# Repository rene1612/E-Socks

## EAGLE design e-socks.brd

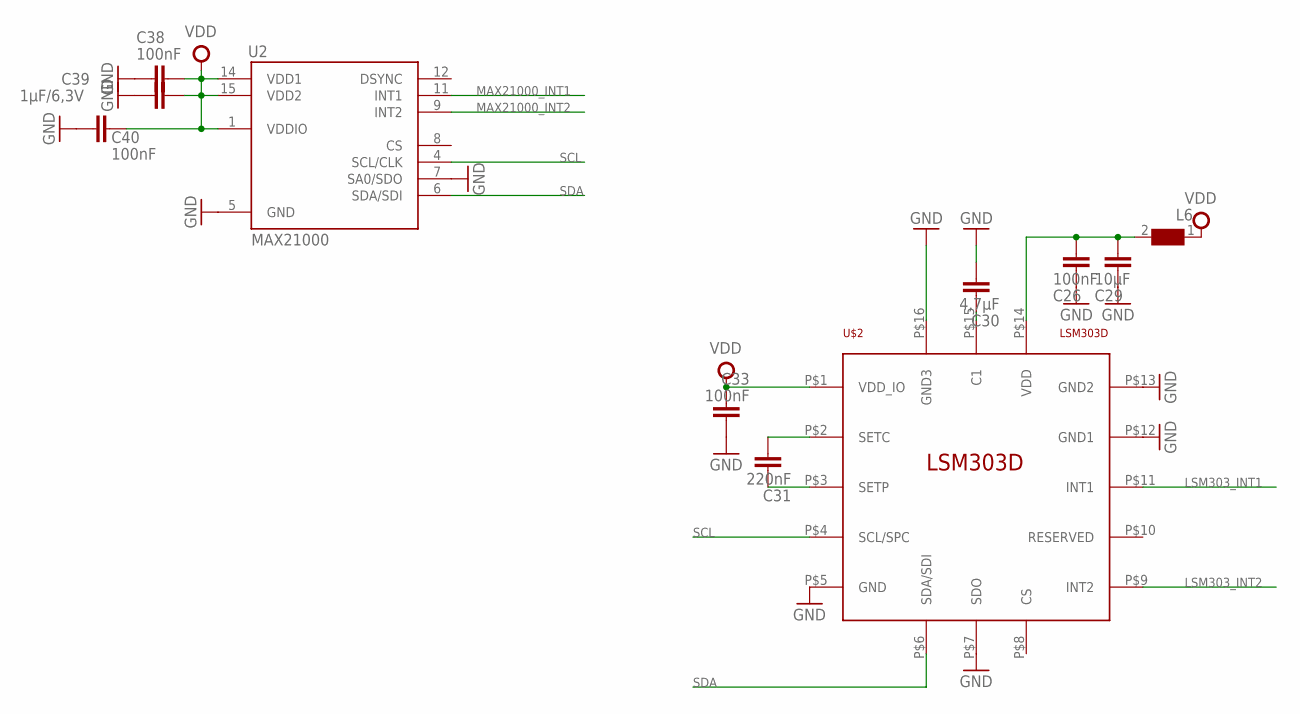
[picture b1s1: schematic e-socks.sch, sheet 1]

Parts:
C26, C33, C38, C40: 100nF; C0402
C29: 10µF; C0402
C30: 4,7µF; C0402
C31: 220nF; C0402
C39: 1µF/6,3V; C0402
L6: WE-CBF_0402; 0402
U2: MAX21000; 16LGA
U$2: LSM303D; TFLGA16L

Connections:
GND: C26.2, C29.2, C30.1, C33.1, C38.2, C39.2, C40.2, U2.5 (GND), U2.7 (SA0/SDO), U$2.P$5 (GND), U$2.P$7 (SDO), U$2.P$12 (GND1), U$2.P$13 (GND2), U$2.P$16 (GND3); also elsewhere on the board
LSM303_INT1: U$2.P$11 (INT1); also elsewhere on the board
LSM303_INT2: U$2.P$9 (INT2)
MAX21000_INT1: U2.11 (INT1); also elsewhere on the board
MAX21000_INT2: U2.9 (INT2)
unnamed: C26.1, C29.1, L6.2, U$2.P$14 (VDD)
unnamed: C31.1, U$2.P$2 (SETC)
unnamed: C31.2, U$2.P$3 (SETP)
unnamed: C30.2, U$2.P$15 (C1)
SCL: U2.4 (SCL/CLK), U$2.P$4 (SCL/SPC); also elsewhere on the board
SDA: U2.6 (SDA/SDI), U$2.P$6 (SDA/SDI); also elsewhere on the board
VDD: C33.2, C38.1, C39.1, C40.1, L6.1, U2.1 (VDDIO), U2.14 (VDD1), U2.15 (VDD2), U$2.P$1 (VDD_IO); also elsewhere on the board

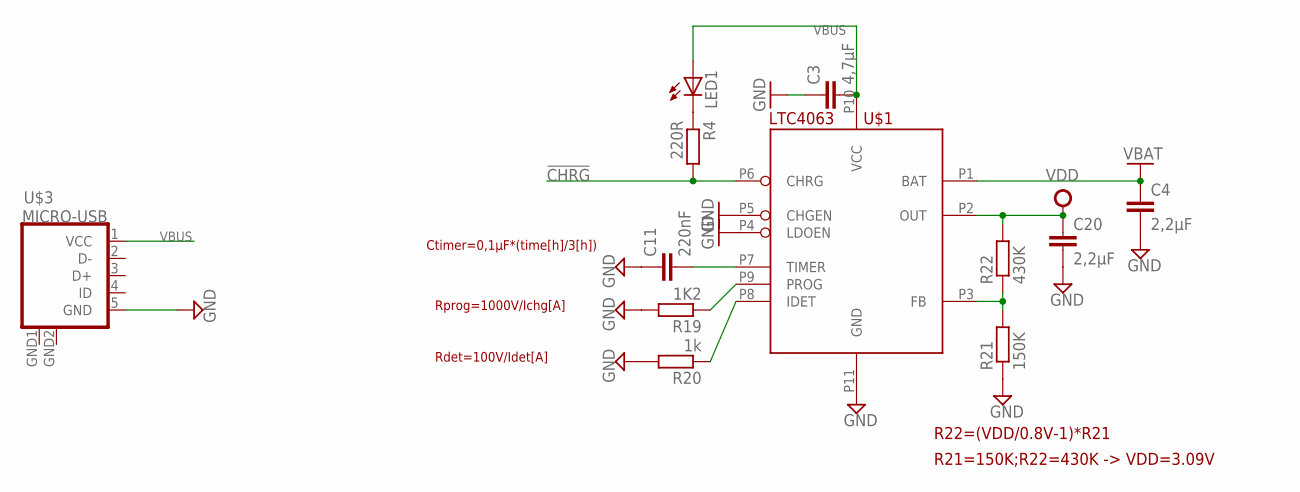
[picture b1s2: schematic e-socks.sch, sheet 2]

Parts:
C3: 4,7µF; C0402
C4, C20: 2,2µF; C0402
C11: 220nF; C0402
LED1: LEDCHIP-LED0603; CHIP-LED0603
R4: 220R; R0402
R19: 1K2; R0402
R20: 1k; R0402
R21: 150K; R0402
R22: 430K; R0402
U$1: LTC4063
U$3: MICRO-USB

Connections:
!CHRG: R4.2, U$1.P6 (CHRG); also elsewhere on the board
GND: C3.1, C4.2, C11.1, C20.2, R19.2, R20.2, R21.1, U$1.P4 (LDOEN), U$1.P5 (CHGEN), U$1.P11 (GND), U$3.5 (GND), U$3.GND1 (GND), U$3.GND2 (GND); also elsewhere on the board
unnamed: C11.2, U$1.P7 (TIMER)
unnamed: R20.1, U$1.P8 (IDET)
unnamed: R21.2, R22.1, U$1.P3 (FB)
unnamed: R19.1, U$1.P9 (PROG)
unnamed: LED1.C, R4.1
VBAT: C4.1, U$1.P1 (BAT); also elsewhere on the board
VBUS: C3.2, LED1.A, U$1.P10 (VCC), U$3.1 (VCC)
VDD: C20.1, R22.2, U$1.P2 (OUT); also elsewhere on the board

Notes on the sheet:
Ctimer=0,1µF*(time[h]/3[h])
Rprog=1000V/Ichg[A]
Rdet=100V/Idet[A]
R22=(VDD/0.8V-1)*R21
R21=150K;R22=430K -> VDD=3.09V

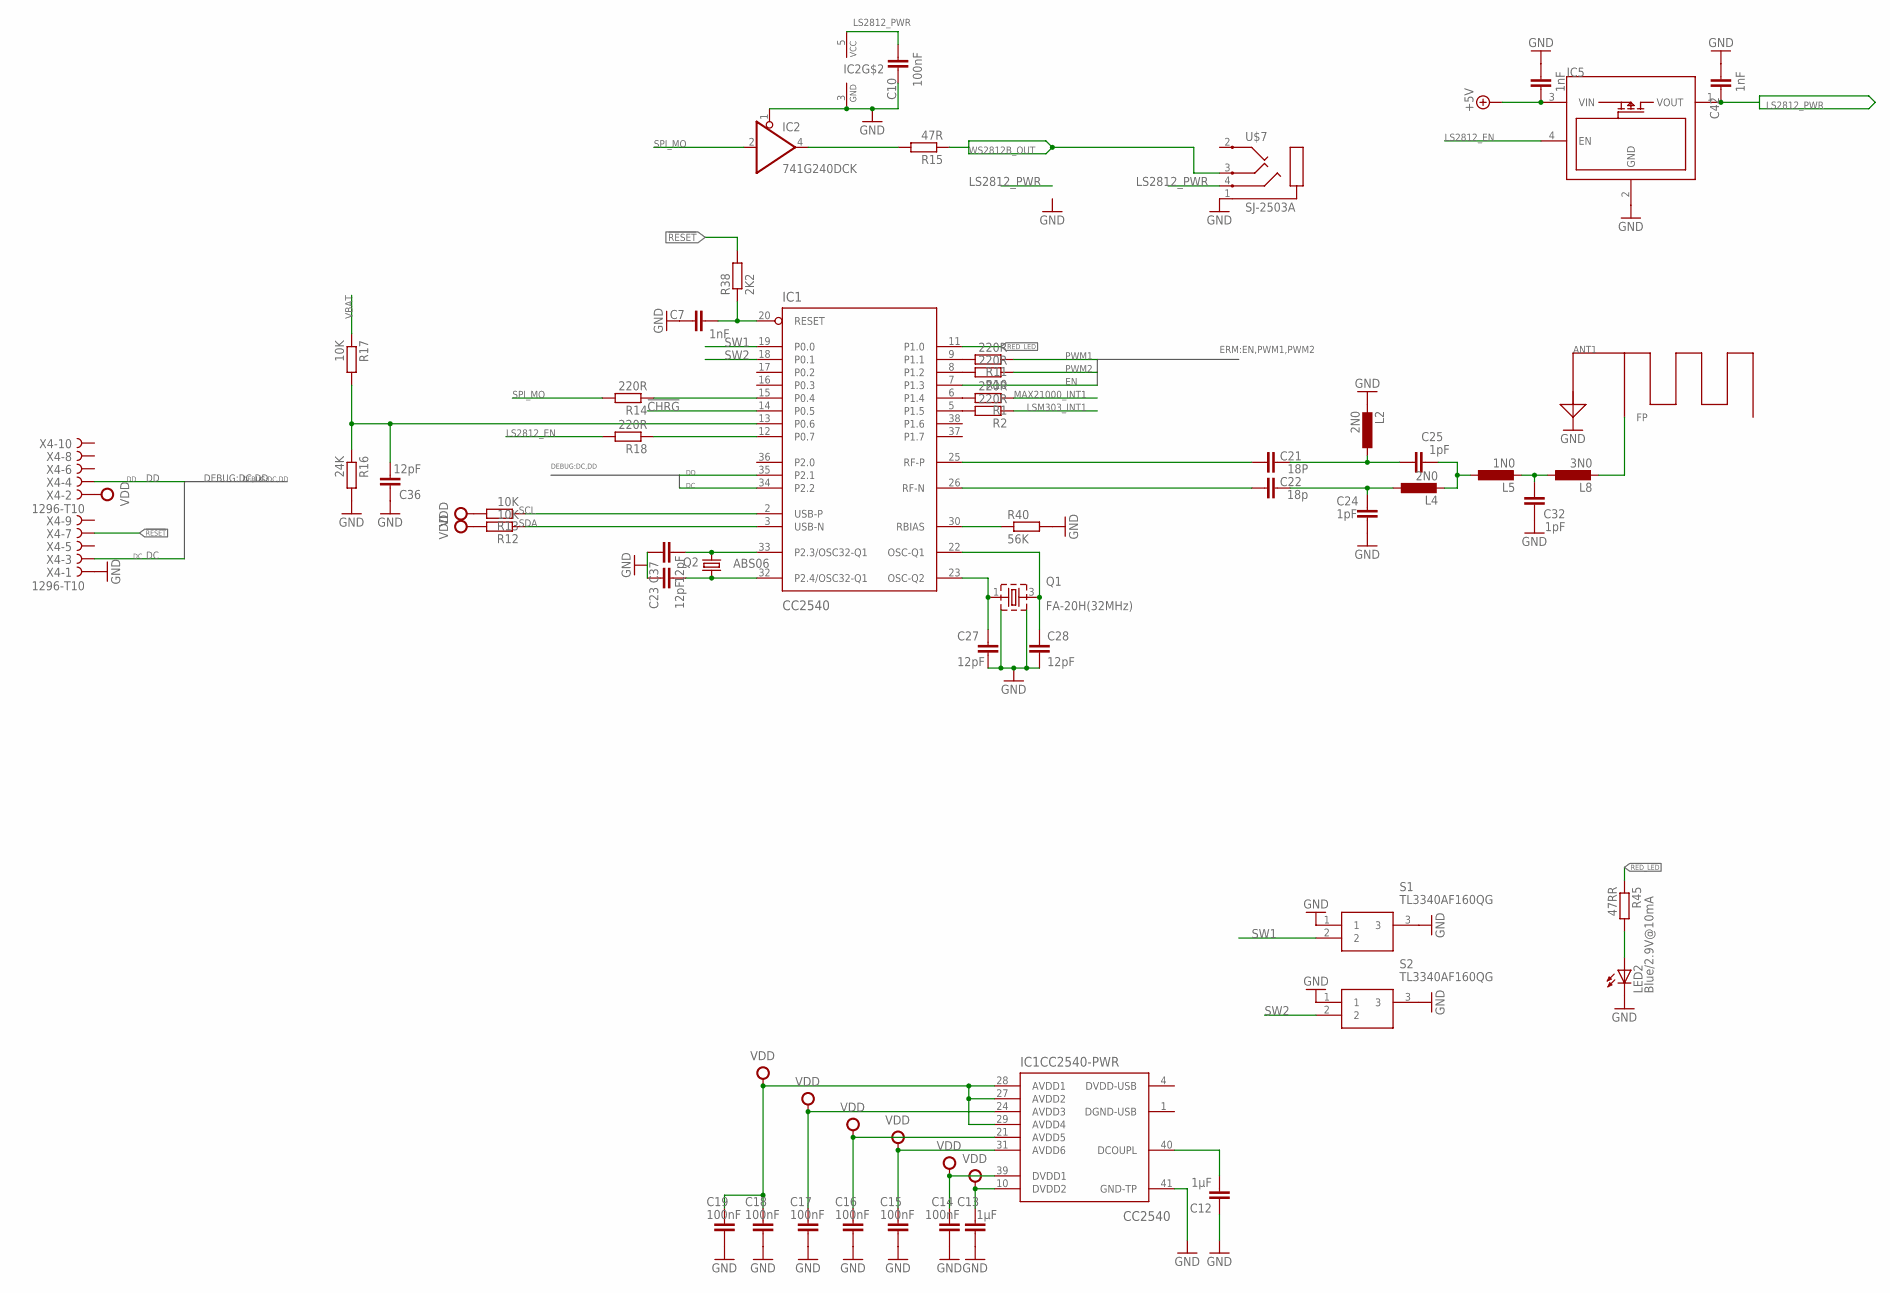
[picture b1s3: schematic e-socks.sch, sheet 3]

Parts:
ANT1: MIFA
C7, C41, C42: 1nF; C0402
C10, C14, C15, C16, C17, C18, C19: 100nF; C0402
C12, C13: 1µF; C0402
C21: 18P; C0402
C22: 18p; C0402
C23, C27, C28, C36, C37: 12pF; C0402
C24, C25, C32: 1pF; C0402
IC1: CC2540; QFN50P600X600X100-41N
IC2: 741G240DCK; SC70-5
IC5: MIC94040
L2, L4: 2N0; L0402
L5: 1N0; L0402
L8: 3N0; L0402
LED2: Blue/2.9V@10mA; CHIP-LED0603
Q1: FA-20H(32MHz); FA-20H
Q2: ABS06
R1, R2, R10, R11, R14, R18: 220R; R0402
R12, R13, R17: 10K; R0402
R15: 47R; R0402
R16: 24K; R0402
R38: 2K2; R0402
R40: 56K; R0402
R45: 47RR; R0402
S1, S2: TL3340AF160QG; TL3340
U$7: SJ-2503A; SJ-2503
X4: 1296-T10; 1296-10

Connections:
!CHRG: IC1.14 (P0.5); also elsewhere on the board
!RESET: R38.2, X4.7
!RESET_INTERN: C7.2, IC1.20 (RESET), R38.1
+5V: C41.1, IC5.3 (VIN); also elsewhere on the board
DC: IC1.34 (P2.2), X4.3
DD: IC1.35 (P2.1), X4.4
DGND-USB: IC1.1 (DGND-USB)
DVDD-USB: IC1.4 (DVDD-USB)
EN: IC1.7 (P1.3); also elsewhere on the board
GND: ANT1.ANT_GND, C7.1, C10.1, C12.1, C13.1, C14.1, C15.1, C16.1, C17.1, C18.1, C19.1, C23.1, C24.1, C27.2, C28.2, C32.2, C36.1, C37.1, C41.2, C42.2, IC1.41 (GND-TP), IC2.1 (OE), IC2.3 (GND), IC5.2 (GND), L2.2, LED2.C, Q1.2 (S1), Q1.4 (S2), R16.2, R40.2, S1.1, S1.3, S2.1, S2.3, U$7.1, X4.1; also elsewhere on the board
LS2812_EN: IC5.4 (EN), R18.2
LS2812_PWR: C10.2, C42.1, IC2.5 (VCC), IC5.1 (VOUT), U$7.4
LSM303_INT1: R1.1; also elsewhere on the board
MAX21000_INT1: R2.1; also elsewhere on the board
unnamed: IC1.6 (P1.4), R1.2
unnamed: IC1.5 (P1.5), R2.2
unnamed: C12.2, IC1.40 (DCOUPL)
unnamed: IC1.8 (P1.2), R10.2
unnamed: LED2.A, R45.2
unnamed: IC1.30 (RBIAS), R40.1
unnamed: C21.2, IC1.25 (RF-P)
unnamed: C22.2, IC1.26 (RF-N)
unnamed: C37.2, IC1.33 (P2.3/OSC32-Q1), Q2.2
unnamed: C23.2, IC1.32 (P2.4/OSC32-Q1), Q2.1
unnamed: IC1.9 (P1.1), R11.2
unnamed: C27.1, IC1.23 (OSC-Q2), Q1.1 (Q1)
unnamed: C28.1, IC1.22 (OSC-Q1), Q1.3 (Q2)
unnamed: IC2.4 (O), R15.2
unnamed: C21.1, C25.2, L2.1
unnamed: C22.1, C24.2, L4.1
unnamed: C25.1, L4.2, L5.1
unnamed: C32.1, L5.2, L8.1
unnamed: ANT1.FP, L8.2
unnamed: IC1.15 (P0.4), R14.1
unnamed: C36.2, IC1.13 (P0.6), R16.1, R17.2
unnamed: IC1.12 (P0.7), R18.1
PWM1: R11.1; also elsewhere on the board
PWM2: R10.1; also elsewhere on the board
RED_LED: IC1.11 (P1.0), R45.1
SCL: IC1.2 (USB-P), R13.1; also elsewhere on the board
SDA: IC1.3 (USB-N), R12.1; also elsewhere on the board
SPI_MO: IC2.2 (I), R14.2
SW1: IC1.19 (P0.0), S1.2
SW2: IC1.18 (P0.1), S2.2
VBAT: R17.1; also elsewhere on the board
VDD: C13.2, C14.2, C15.2, C16.2, C17.2, C18.2, C19.2, IC1.10 (DVDD2), IC1.21 (AVDD5), IC1.24 (AVDD3), IC1.27 (AVDD2), IC1.28 (AVDD1), IC1.29 (AVDD4), IC1.31 (AVDD6), IC1.39 (DVDD1), R12.2, R13.2, X4.2; also elsewhere on the board
WS2812B_OUT: R15.1, U$7.3

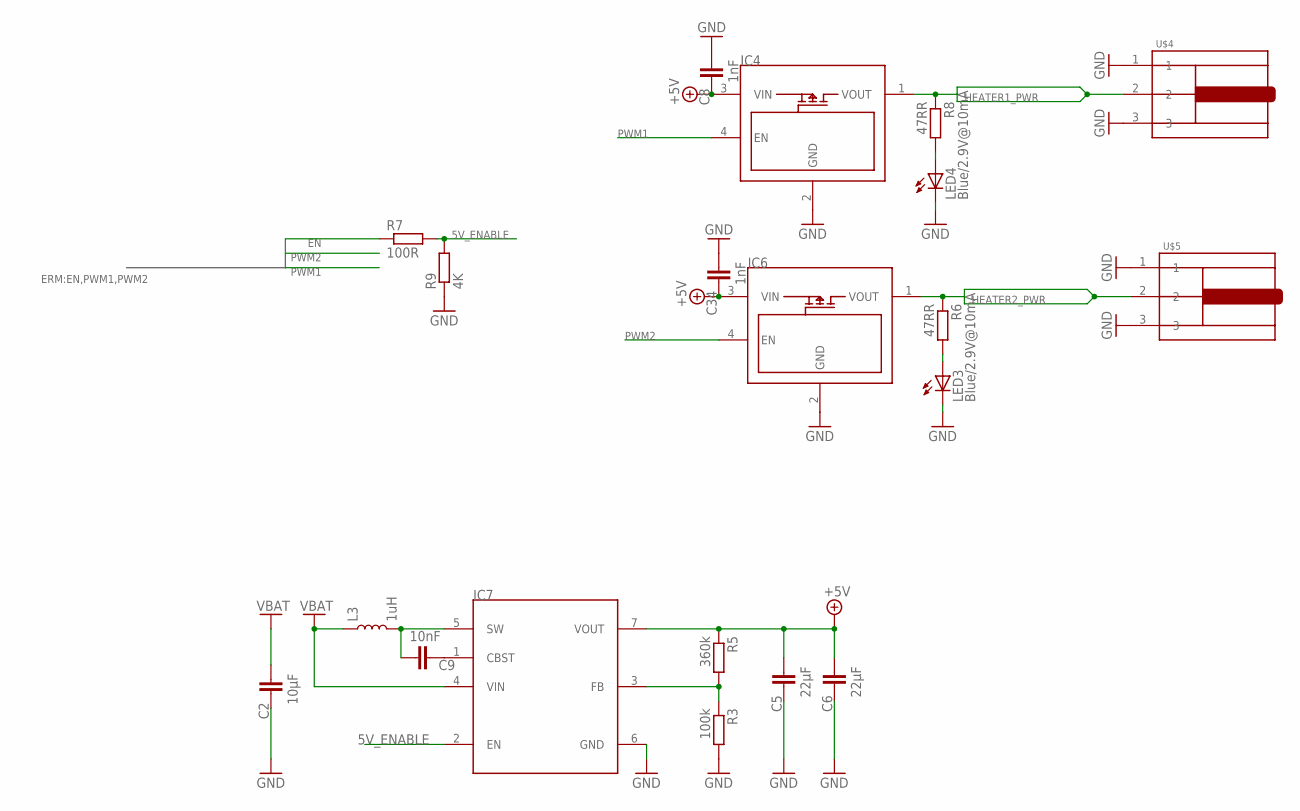
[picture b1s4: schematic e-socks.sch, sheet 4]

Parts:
C2: 10µF; C0603
C5, C6: 22µF; C0805
C8, C34: 1nF; C0402
C9: 10nF; C0402
IC4, IC6: MIC94040
IC7: TPS61230AVQFN; VQFN
L3: 1uH; XFL4020
LED3, LED4: Blue/2.9V@10mA; CHIP-LED0603
R3: 100k; R0402
R5: 360k; R0402
R6, R8: 47RR; R0402
R7: 100R; R0402
R9: 4K; R0402
U$4, U$5: JACKJACK; JACK

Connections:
5V_ENABLE: IC7.2 (EN), R7.2, R9.2
+5V: C5.2, C6.2, C8.1, C34.1, IC4.3 (VIN), IC6.3 (VIN), IC7.7 (VOUT), R5.1; also elsewhere on the board
EN: R7.1; also elsewhere on the board
GND: C2.1, C5.1, C6.1, C8.2, C34.2, IC4.2 (GND), IC6.2 (GND), IC7.6 (GND), LED3.C, LED4.C, R3.2, R9.1, U$4.1, U$4.3, U$5.1, U$5.3; also elsewhere on the board
HEATER1_PWR: IC4.1 (VOUT), R8.1, U$4.2
HEATER2_PWR: IC6.1 (VOUT), R6.1, U$5.2
unnamed: LED3.A, R6.2
unnamed: LED4.A, R8.2
unnamed: IC7.3 (FB), R3.1, R5.2
unnamed: C9.2, IC7.5 (SW), L3.P$2 (2)
unnamed: C9.1, IC7.1 (CBST)
PWM1: IC4.4 (EN); also elsewhere on the board
PWM2: IC6.4 (EN); also elsewhere on the board
VBAT: C2.2, IC7.4 (VIN), L3.P$1 (1); also elsewhere on the board

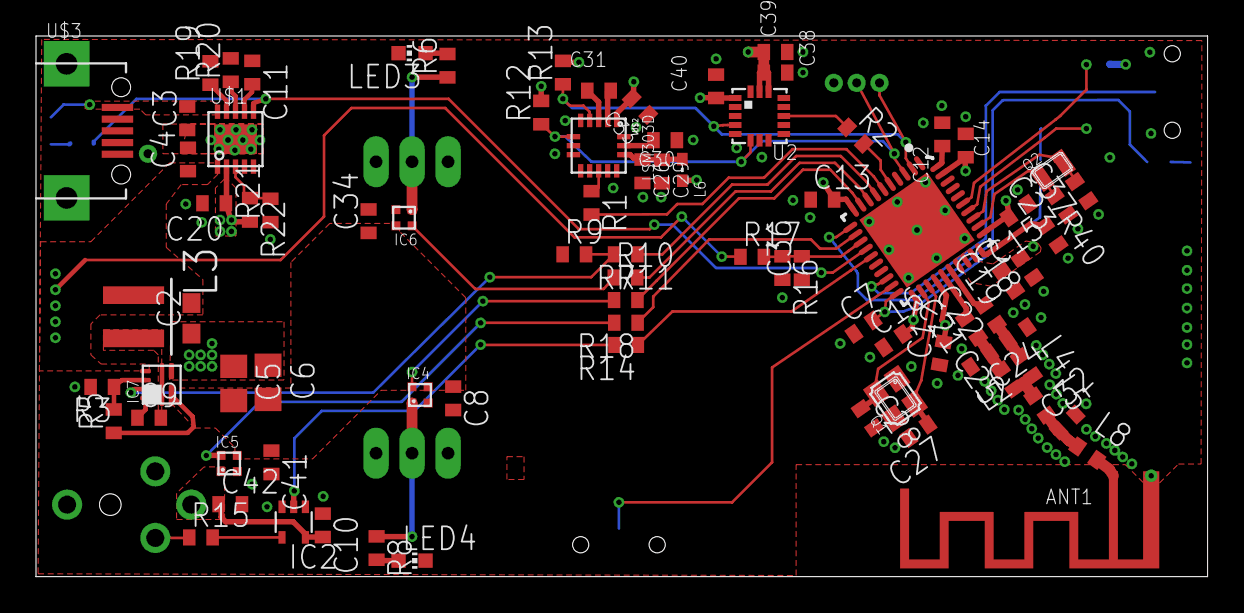
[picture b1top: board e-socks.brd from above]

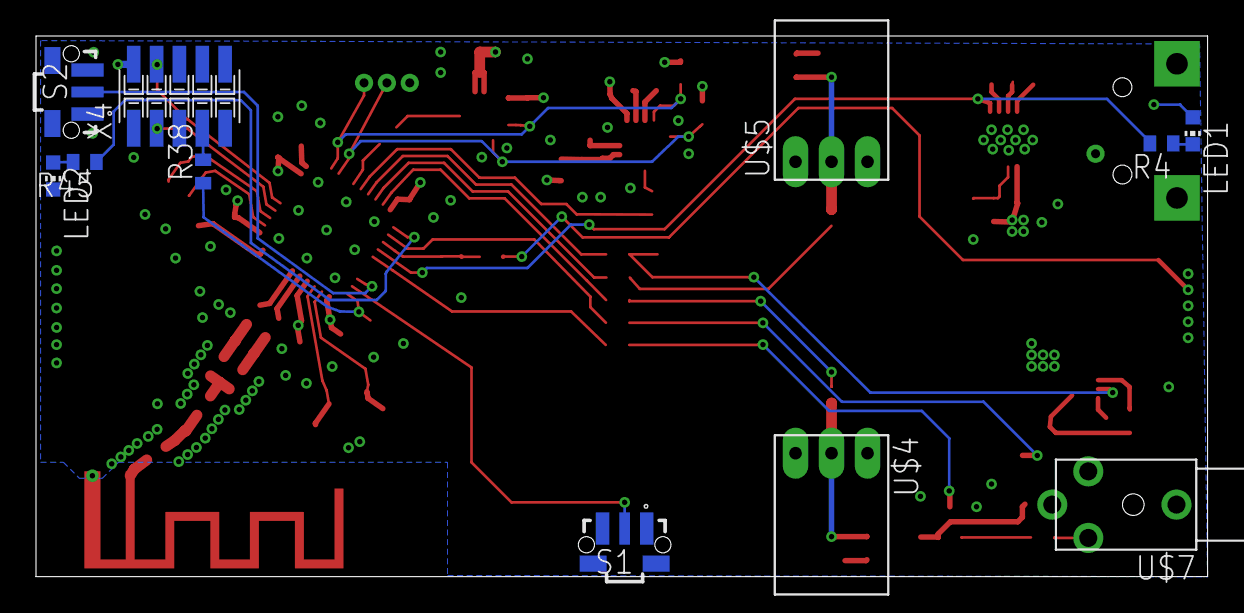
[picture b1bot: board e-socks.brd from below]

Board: 4 copper layers, 65.1 x 30.0 mm, 94 parts (11 on the bottom side), 63 nets.

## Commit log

2018-10-24 erstes Commit
2018-10-25 erstes commit für diesen branch
2018-10-26 taster getauscht, 2.5mm klinke hinzugefügt, noch nicht geroutet
2018-10-27 routing fertig @home
2018-11-29 4K Pulldown Widerstand hinzugefügt, um den Pullup Widerstand im Reset zu überstimmen (nur für 5V-Enable), einige Widerstandswerte angepasst)

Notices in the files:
parts and their libraries:
SparkFun-Coils: Licensing: Creative Commons ShareAlike 4.0 International - https://creativecommons.org/licenses/by-sa/4.0
supply0: Copyright (C) 2007, Bob Starr
LinearTechnology: Copyright (c) 2013, Michael Hohl
